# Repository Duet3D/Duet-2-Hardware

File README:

The Duet 3D Printer Controller design files repository.

The latest Duet hardware is the DuetWifi, see https://www.duet3d.com/ for more information

The recommended firmware is DC42's branch of the RepRapFirmware:
https://github.com/dc42/RepRapFirmware

Duet 2 Wifi and Duet 2 Ethernet
Design by Tony Lock and David Crocker
More info:
https://www.duet3d.com/
LICENSE: see the LICENSE file in the repository

Duet 0.8.5
Design by Tony Lock, based on the Duet 0.6
More info here:
http://blog.think3dprint3d.com/2015/08/new-duet-electronics-version-085.html
LICENSE: http://www.ohwr.org/attachments/2388/cern_ohl_v_1_2.txt

Duet 0.6:
Design by Andy Hingston, Tony Lock, Adrian Bowyer with much advice from Chris Palmer.
More info here:
http://blog.think3dprint3d.com/2013/12/Duet-Arduino-Due-compatible-3DPrinter-controller.html
LICENSE: http://www.ohwr.org/attachments/2388/cern_ohl_v_1_2.txt

Developed in KiCAD: http://www.kicad-pcb.org/display/KICAD/KiCad+EDA+Software+Suite

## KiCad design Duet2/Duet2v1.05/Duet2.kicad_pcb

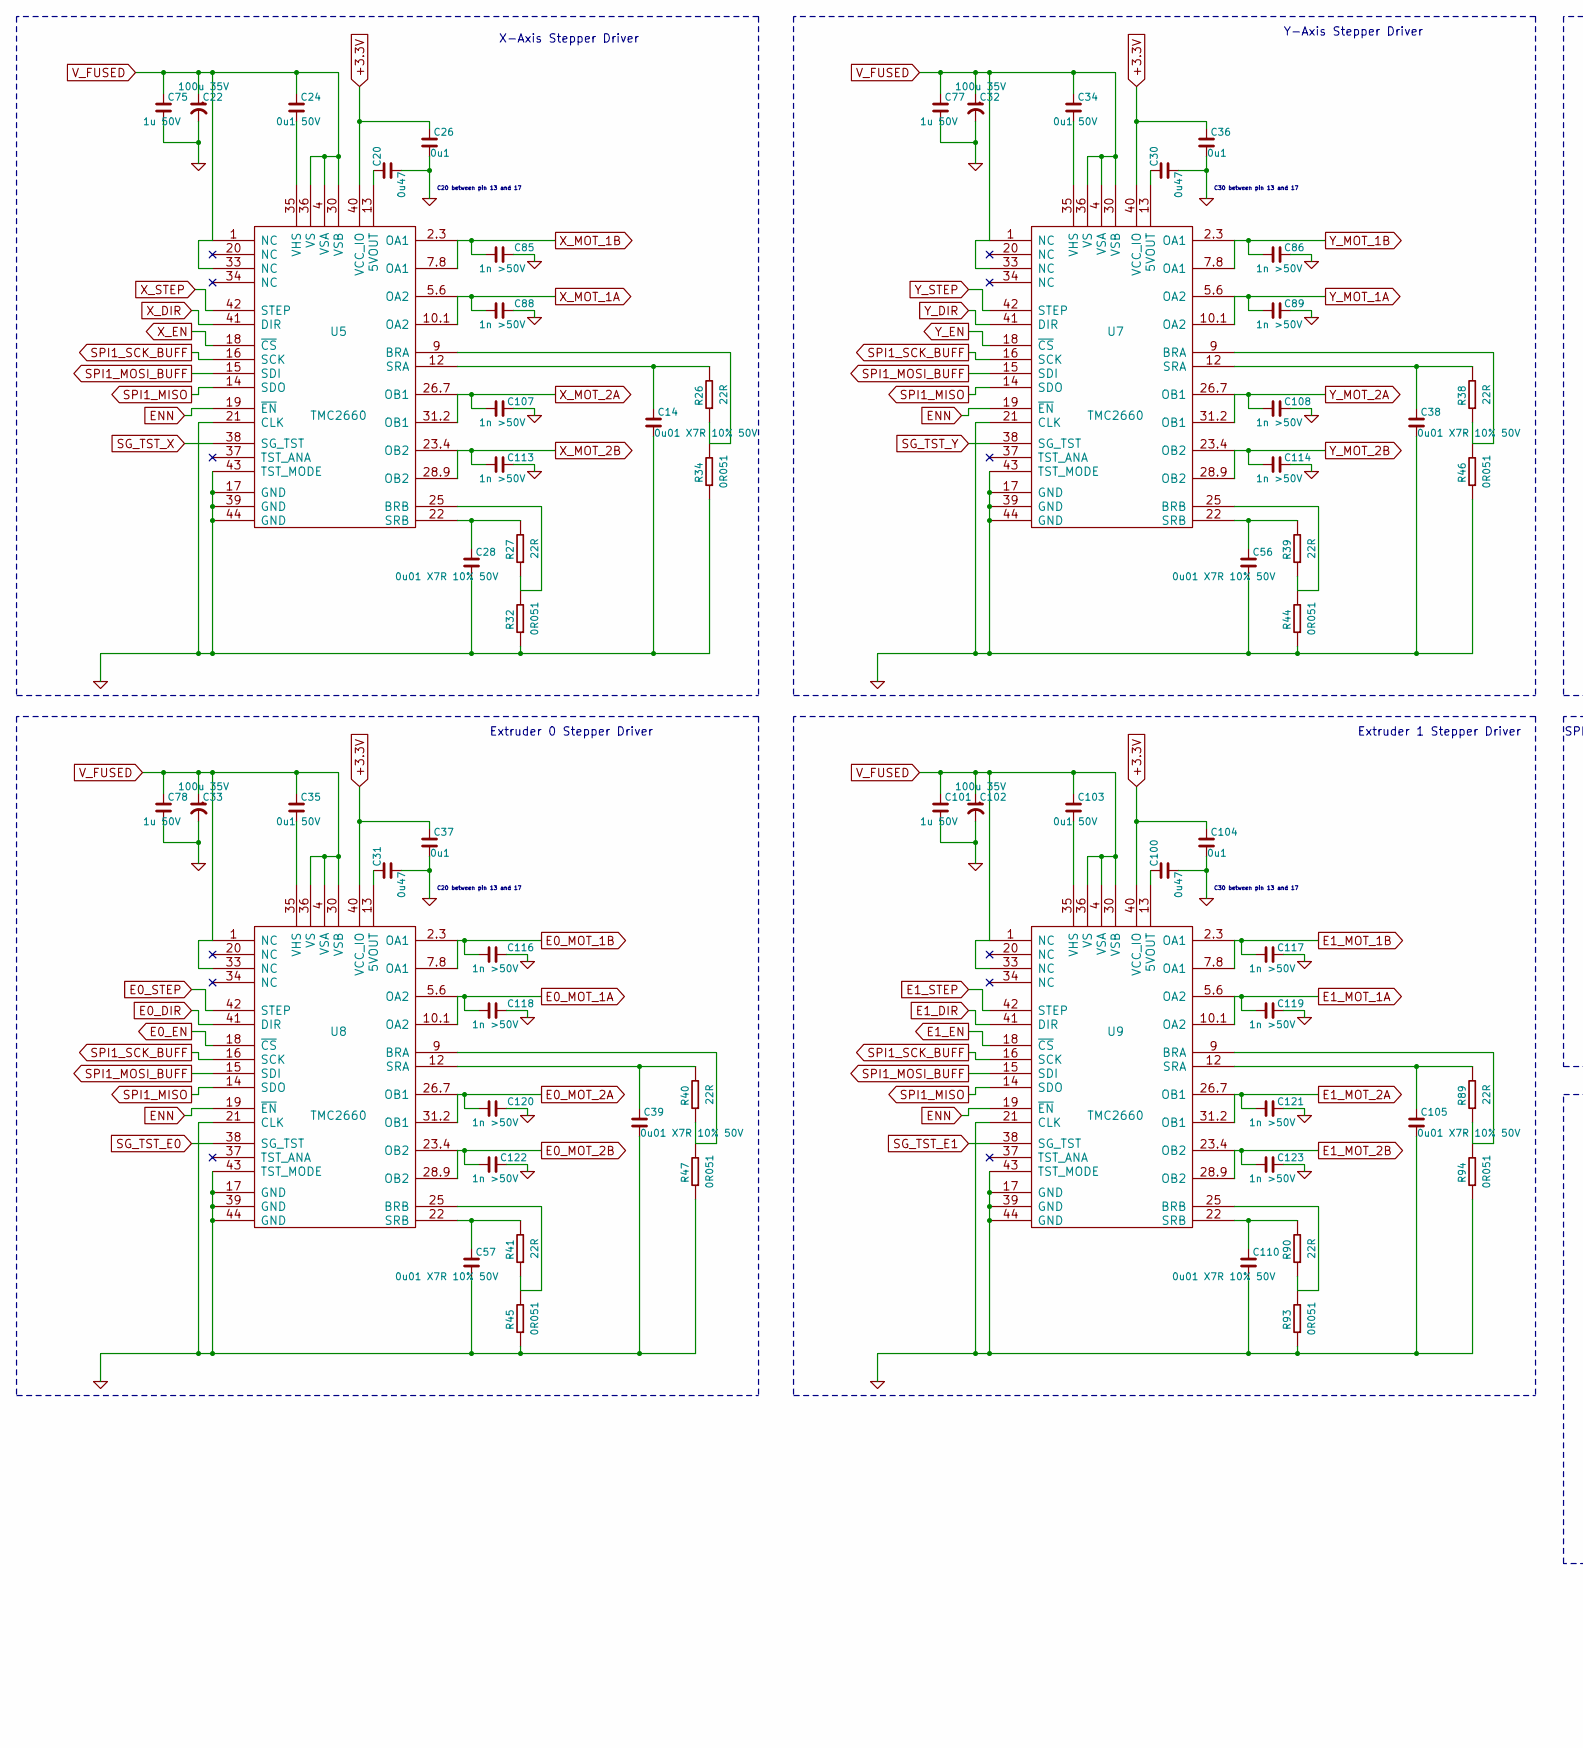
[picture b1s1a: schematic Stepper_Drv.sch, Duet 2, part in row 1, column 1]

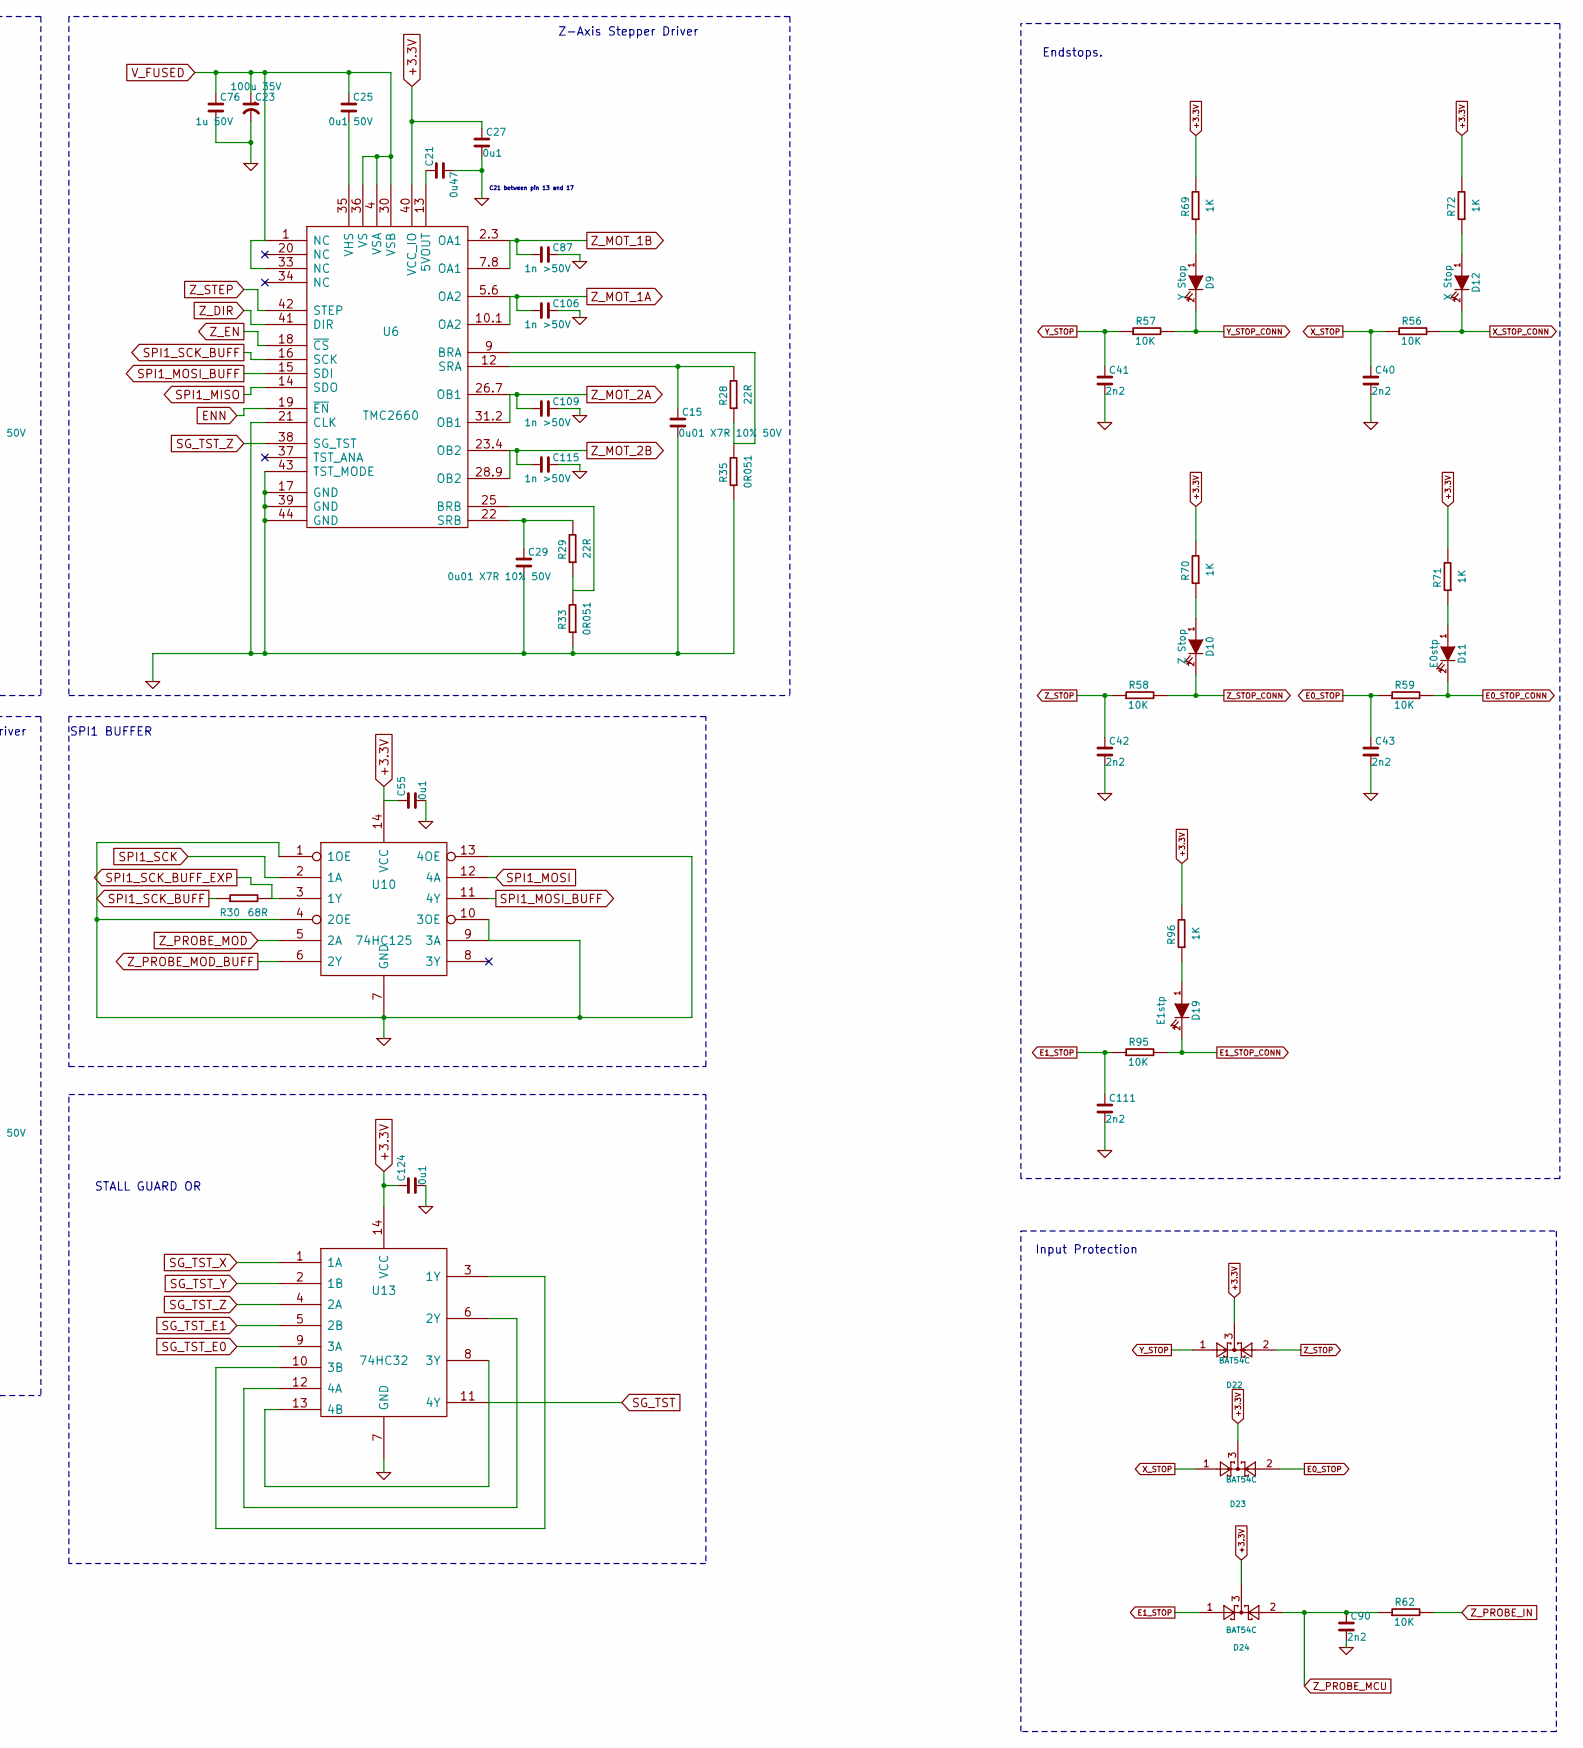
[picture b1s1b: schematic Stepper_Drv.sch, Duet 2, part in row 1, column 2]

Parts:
C14, C15, C28, C29, C38, C39, C56, C57, C105, C110: 0u01 X7R 10% 50V; C_0603
C20, C21, C30, C31, C100: 0u47; C_0603
C22, C23, C32, C33, C102: 100u 35V; C_ELEC_6.3x7.7
C24, C25, C34, C35, C103: 0u1 50V; C_0603
C26, C27, C36, C37, C55, C104, C124: 0u1; C_0603
C40, C41, C42, C43, C90, C111: 2n2; C_0603
C75, C76, C77, C78, C101: 1u 50V; C_0603
C85, C86, C87, C88, C89, C106, C107, C108, C109, C113, C114, C115, C116, C117, C118, C119, C120, C121, C122, C123: 1n >50V; C_0603
D9: Y Stop; D_0603
D10: Z Stop; D_0603
D11: E0stp; D_0603
D12: X Stop; D_0603
D19: E1stp; D_0603
D22, D23, D24: BAT54C; SOT-23-D
R26, R27, R28, R29, R38, R39, R40, R41, R89, R90: 22R; R_0603
R30: 68R; R_0603
R32, R33, R34, R35, R44, R45, R46, R47, R93, R94: 0R051; R_1206
R56, R57, R58, R59, R62, R95: 10K; R_0603
R69, R70, R71, R72, R96: 1K; R_0603
U5, U6, U7, U8, U9: TMC2660
U10: 74HC125; TSSOP-14
U13: 74HC32; TSSOP-14

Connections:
+3.3V: C26.1, C27.1, C36.1, C37.1, C55.1, C104.1, C124.1, D22.3, D23.3, D24.3, R69.2, R70.2, R71.2, R72.2, R96.2, U5.40 (VCC_IO), U6.40 (VCC_IO), U7.40 (VCC_IO), U8.40 (VCC_IO), U9.40 (VCC_IO), U10.14 (VCC), U13.14 (VCC); also elsewhere on the board
E0_DIR: U8.41 (DIR); also elsewhere on the board
E0_EN: U8.18 (~CS); also elsewhere on the board
E0_MOT_1A: C118.2, U8.5.6 (OA2), U8.10.1 (OA2); also elsewhere on the board
E0_MOT_1B: C116.2, U8.2.3 (OA1), U8.7.8 (OA1); also elsewhere on the board
E0_MOT_2A: C120.2, U8.26.7 (OB1), U8.31.2 (OB1); also elsewhere on the board
E0_MOT_2B: C122.2, U8.23.4 (OB2), U8.28.9 (OB2); also elsewhere on the board
E0_STEP: U8.42 (STEP); also elsewhere on the board
E0_STOP: C43.1, D23.2, R59.1; also elsewhere on the board
E0_STOP_CONN: D11.2 (K), R59.2; also elsewhere on the board
E1_DIR: U9.41 (DIR); also elsewhere on the board
E1_EN: U9.18 (~CS); also elsewhere on the board
E1_MOT_1A: C119.2, U9.5.6 (OA2), U9.10.1 (OA2); also elsewhere on the board
E1_MOT_1B: C117.2, U9.2.3 (OA1), U9.7.8 (OA1); also elsewhere on the board
E1_MOT_2A: C121.2, U9.26.7 (OB1), U9.31.2 (OB1); also elsewhere on the board
E1_MOT_2B: C123.2, U9.23.4 (OB2), U9.28.9 (OB2); also elsewhere on the board
E1_STEP: U9.42 (STEP); also elsewhere on the board
E1_STOP: C111.1, D24.1, R95.1; also elsewhere on the board
E1_STOP_CONN: D19.2 (K), R95.2; also elsewhere on the board
ENN: U5.19 (~EN), U6.19 (~EN), U7.19 (~EN), U8.19 (~EN), U9.19 (~EN); also elsewhere on the board
GND: C14.2, C15.2, C20.2, C21.2, C22.2, C23.2, C26.2, C27.2, C28.2, C29.2, C30.2, C31.2, C32.2, C33.2, C36.2, C37.2, C38.2, C39.2, C40.2, C41.2, C42.2, C43.2, C55.2, C56.2, C57.2, C75.2, C76.2, C77.2, C78.2, C85.1, C86.1, C87.1, C88.1, C89.1, C90.2, C100.2, C101.2, C102.2, C104.2, C105.2, C106.1, C107.1, C108.1, C109.1, C110.2, C111.2, C113.1, C114.1, C115.1, C116.1, C117.1, C118.1, C119.1, C120.1, C121.1, C122.1, C123.1, C124.2, R32.1, R33.1, R34.1, R35.1, R44.1, R45.1, R46.1, R47.1, R93.1, R94.1, U5.17 (GND), U5.21 (CLK), U5.39 (GND), U5.43 (TST_MODE), U5.44 (GND), U6.17 (GND), U6.21 (CLK), U6.39 (GND), U6.43 (TST_MODE), U6.44 (GND), U7.17 (GND), U7.21 (CLK), U7.39 (GND), U7.43 (TST_MODE), U7.44 (GND), U8.17 (GND), U8.21 (CLK), U8.39 (GND), U8.43 (TST_MODE), U8.44 (GND), U9.17 (GND), U9.21 (CLK), U9.39 (GND), U9.43 (TST_MODE), U9.44 (GND), U10.1 (1OE), U10.4 (2OE), U10.7 (GND), U10.9 (3A), U10.10 (3OE), U10.13 (4OE), U13.7 (GND); also elsewhere on the board
unnamed: C14.1, R26.2, U5.12 (SRA)
unnamed: C15.1, R28.2, U6.12 (SRA)
unnamed: C20.1, U5.13 (5VOUT)
unnamed: C21.1, U6.13 (5VOUT)
unnamed: C24.2, U5.35 (VHS)
unnamed: C25.2, U6.35 (VHS)
unnamed: C28.1, R27.2, U5.22 (SRB)
unnamed: C29.1, R29.2, U6.22 (SRB)
unnamed: C30.1, U7.13 (5VOUT)
unnamed: C31.1, U8.13 (5VOUT)
unnamed: C34.2, U7.35 (VHS)
unnamed: C35.2, U8.35 (VHS)
unnamed: C38.1, R38.2, U7.12 (SRA)
unnamed: C39.1, R40.2, U8.12 (SRA)
unnamed: C56.1, R39.2, U7.22 (SRB)
unnamed: C57.1, R41.2, U8.22 (SRB)
unnamed: C100.1, U9.13 (5VOUT)
unnamed: C103.2, U9.35 (VHS)
unnamed: C105.1, R89.2, U9.12 (SRA)
unnamed: C110.1, R90.2, U9.22 (SRB)
unnamed: D9.1 (A), R69.1
unnamed: D10.1 (A), R70.1
unnamed: D11.1 (A), R71.1
unnamed: D12.1 (A), R72.1
unnamed: D19.1 (A), R96.1
unnamed: R26.1, R34.2, U5.9 (BRA)
unnamed: R27.1, R32.2, U5.25 (BRB)
unnamed: R28.1, R35.2, U6.9 (BRA)
unnamed: R29.1, R33.2, U6.25 (BRB)
unnamed: R38.1, R46.2, U7.9 (BRA)
unnamed: R39.1, R44.2, U7.25 (BRB)
unnamed: R40.1, R47.2, U8.9 (BRA)
unnamed: R41.1, R45.2, U8.25 (BRB)
unnamed: R89.1, R94.2, U9.9 (BRA)
unnamed: R90.1, R93.2, U9.25 (BRB)
unnamed: U13.3 (1Y), U13.10 (3B)
unnamed: U13.6 (2Y), U13.12 (4A)
unnamed: U13.8 (3Y), U13.13 (4B)
PB5/TDO: U13.11 (4Y); also elsewhere on the board
SG_TST_E0: U8.38 (SG_TST), U13.9 (3A)
SG_TST_E1: U9.38 (SG_TST), U13.5 (2B)
SG_TST_X: U5.38 (SG_TST), U13.1 (1A)
SG_TST_Y: U7.38 (SG_TST), U13.2 (1B)
SG_TST_Z: U6.38 (SG_TST), U13.4 (2A)
SPI1_MISO: U5.14 (SDO), U6.14 (SDO), U7.14 (SDO), U8.14 (SDO), U9.14 (SDO); also elsewhere on the board
SPI1_MOSI: U10.12 (4A); also elsewhere on the board
SPI1_MOSI_BUFF: U5.15 (SDI), U6.15 (SDI), U7.15 (SDI), U8.15 (SDI), U9.15 (SDI), U10.11 (4Y); also elsewhere on the board
SPI1_SCK: U10.2 (1A); also elsewhere on the board
SPI1_SCK_BUFF: R30.1, U5.16 (SCK), U6.16 (SCK), U7.16 (SCK), U8.16 (SCK), U9.16 (SCK); also elsewhere on the board
SPI1_SCK_BUFF_EXP: R30.2, U10.3 (1Y); also elsewhere on the board
V_FUSED: C22.1, C23.1, C24.1, C25.1, C32.1, C33.1, C34.1, C35.1, C75.1, C76.1, C77.1, C78.1, C101.1, C102.1, C103.1, U5.1 (NC), U5.4 (VSA), U5.30 (VSB), U5.33 (NC), U5.36 (VS), U6.1 (NC), U6.4 (VSA), U6.30 (VSB), U6.33 (NC), U6.36 (VS), U7.1 (NC), U7.4 (VSA), U7.30 (VSB), U7.33 (NC), U7.36 (VS), U8.1 (NC), U8.4 (VSA), U8.30 (VSB), U8.33 (NC), U8.36 (VS), U9.1 (NC), U9.4 (VSA), U9.30 (VSB), U9.33 (NC), U9.36 (VS); also elsewhere on the board
X_DIR: U5.41 (DIR); also elsewhere on the board
X_EN: U5.18 (~CS); also elsewhere on the board
X_MOT_1A: C88.2, U5.5.6 (OA2), U5.10.1 (OA2); also elsewhere on the board
X_MOT_1B: C85.2, U5.2.3 (OA1), U5.7.8 (OA1); also elsewhere on the board
X_MOT_2A: C107.2, U5.26.7 (OB1), U5.31.2 (OB1); also elsewhere on the board
X_MOT_2B: C113.2, U5.23.4 (OB2), U5.28.9 (OB2); also elsewhere on the board
X_STEP: U5.42 (STEP); also elsewhere on the board
X_STOP: C40.1, D23.1, R56.1; also elsewhere on the board
X_STOP_CONN: D12.2 (K), R56.2; also elsewhere on the board
Y_DIR: U7.41 (DIR); also elsewhere on the board
Y_EN: U7.18 (~CS); also elsewhere on the board
Y_MOT_1A: C89.2, U7.5.6 (OA2), U7.10.1 (OA2); also elsewhere on the board
Y_MOT_1B: C86.2, U7.2.3 (OA1), U7.7.8 (OA1); also elsewhere on the board
Y_MOT_2A: C108.2, U7.26.7 (OB1), U7.31.2 (OB1); also elsewhere on the board
Y_MOT_2B: C114.2, U7.23.4 (OB2), U7.28.9 (OB2); also elsewhere on the board
Y_STEP: U7.42 (STEP); also elsewhere on the board
Y_STOP: C41.1, D22.1, R57.1; also elsewhere on the board
Y_STOP_CONN: D9.2 (K), R57.2; also elsewhere on the board
Z_DIR: U6.41 (DIR); also elsewhere on the board
Z_EN: U6.18 (~CS); also elsewhere on the board
Z_MOT_1A: C106.2, U6.5.6 (OA2), U6.10.1 (OA2); also elsewhere on the board
Z_MOT_1B: C87.2, U6.2.3 (OA1), U6.7.8 (OA1); also elsewhere on the board
Z_MOT_2A: C109.2, U6.26.7 (OB1), U6.31.2 (OB1); also elsewhere on the board
Z_MOT_2B: C115.2, U6.23.4 (OB2), U6.28.9 (OB2); also elsewhere on the board
Z_PROBE_IN: R62.2; also elsewhere on the board
Z_PROBE_MCU: C90.1, D24.2, R62.1; also elsewhere on the board
Z_PROBE_MOD: U10.5 (2A); also elsewhere on the board
Z_PROBE_MOD_BUFF: U10.6 (2Y); also elsewhere on the board
Z_STEP: U6.42 (STEP); also elsewhere on the board
Z_STOP: C42.1, D22.2, R58.1; also elsewhere on the board
Z_STOP_CONN: D10.2 (K), R58.2; also elsewhere on the board

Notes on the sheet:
Endstops.
Extruder 0 Stepper Driver
Y-Axis Stepper Driver
X-Axis Stepper Driver
Extruder 1 Stepper Driver
SPI1 BUFFER
C20 between pin 13 and 17
C30 between pin 13 and 17
Z-Axis Stepper Driver
C21 between pin 13 and 17
STALL GUARD OR
Input Protection

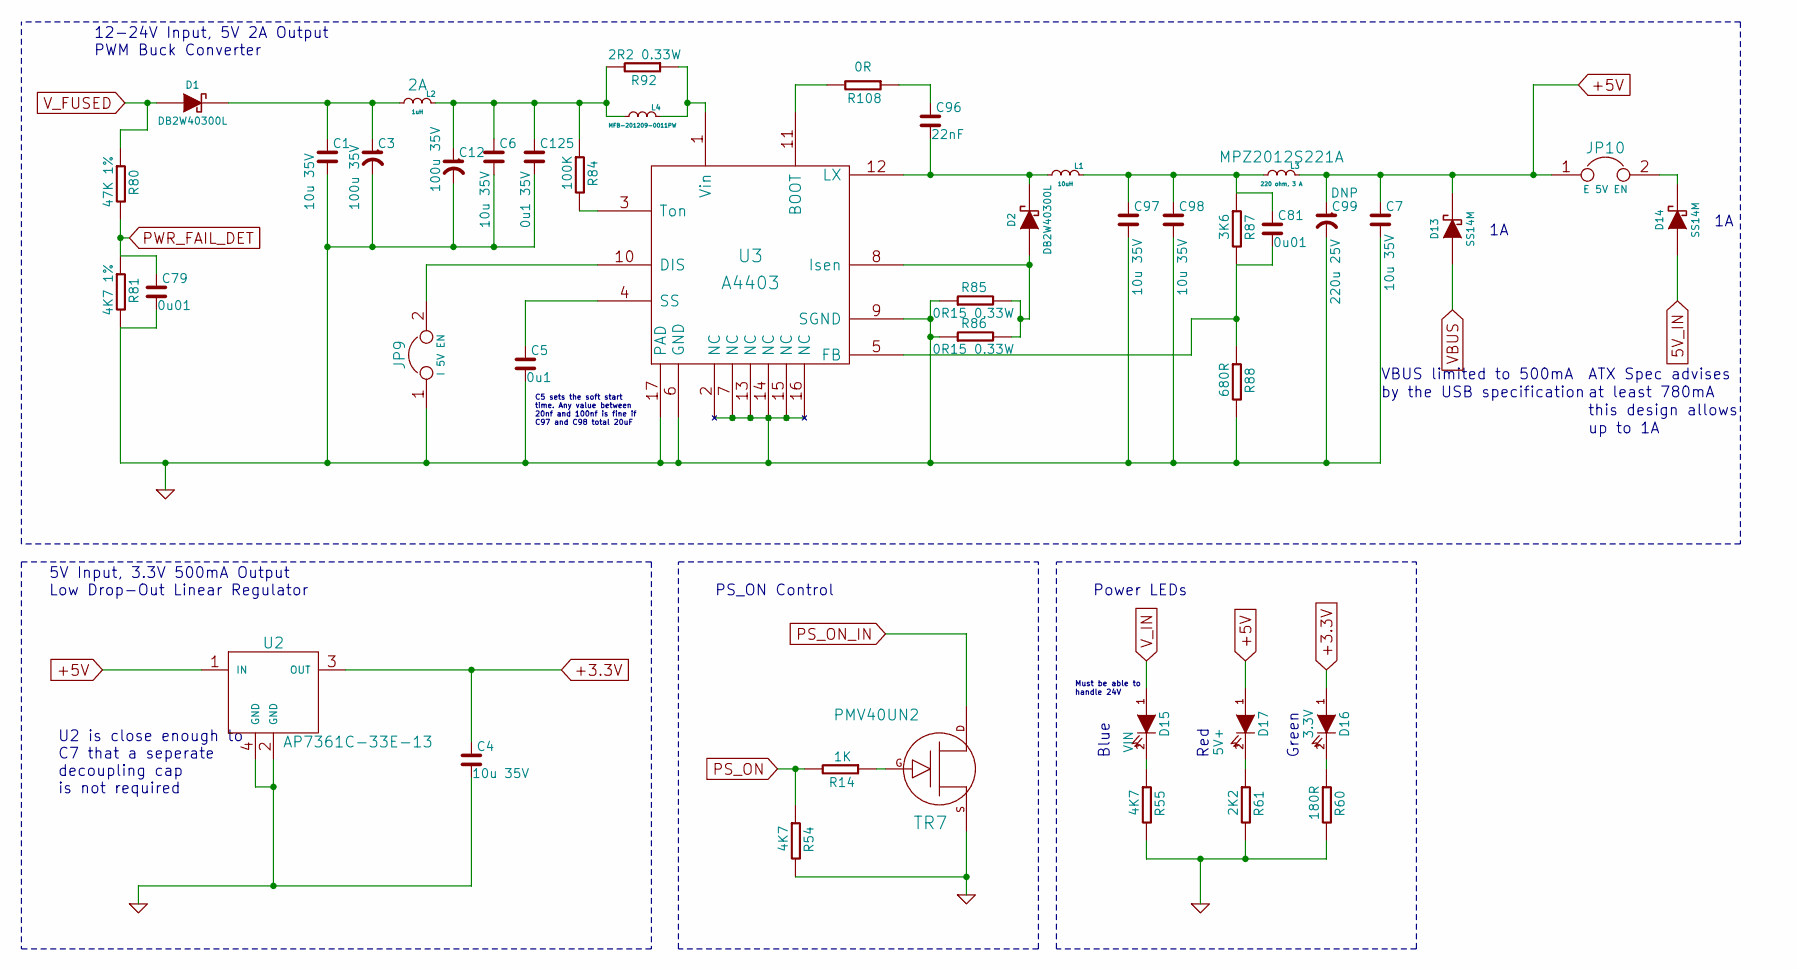
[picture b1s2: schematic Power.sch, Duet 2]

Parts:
C1, C4, C6, C7, C97, C98: 10u 35V; C_1206
C3, C12: 100u 35V; C_ELEC_6.3x7.7
C5: 0u1; C_0603
C79, C81: 0u01; C_0603
C96: 22nF; C_0603
C99: 220u 25V; C_ELEC_6.3x7.7; Rating DNP
C125: 0u1 35V; C_0603
D1, D2: DB2W40300L; D_SOD-123F
D13, D14: SS14M; uSMA
D15: VIN; D_0603
D16: 3.3V; D_0603
D17: 5V+; D_0603
JP9: I 5V EN; JUMPER
JP10: E 5V EN; JUMPER
L1: 10uH; L_6x6
L2: 1uH; C_1210; Rating 2A
L3: 220 ohm, 3 A; R_0805; Rating MPZ2012S221A
L4: MFB-201209-0011PW; R_0805
R14: 1K; R_0603
R54, R55: 4K7; R_0603
R60: 180R; R_0603
R61: 2K2; R_0603
R80: 47K 1%; R_0603
R81: 4K7 1%; R_0603
R84: 100K; R_0603
R85, R86: 0R15 0.33W; R_0805
R87: 3K6; R_0603
R88: 680R; R_0603
R92: 2R2 0.33W; R_0805
R108: 0R; R_0603
TR7: PMV40UN2; SOT-23
U2: AP7361C-33E-13; SOT-223
U3: A4403; QFN16-4x4

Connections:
5V_IN: D14.1 (A); also elsewhere on the board
+3.3V: C4.1, D16.1 (A), U2.3 (OUT); also elsewhere on the board
+5V: C7.1, C99.1, D13.2 (K), D17.1 (A), JP10.1, L3.1 (A), U2.1 (IN); also elsewhere on the board
GND: C1.2, C3.2, C4.2, C5.2, C6.2, C7.2, C12.2, C79.2, C97.2, C98.2, C99.2, C125.2, JP9.1, R54.2, R55.2, R60.2, R61.2, R81.2, R85.1, R86.1, R88.2, TR7.S, U2.2 (GND), U2.4 (GND), U3.2 (NC), U3.6 (GND), U3.7 (NC), U3.9 (SGND), U3.13 (NC), U3.14 (NC), U3.15 (NC), U3.16 (NC), U3.17 (PAD); also elsewhere on the board
unnamed: C1.1, C3.1, D1.1 (K), L2.2 (B)
unnamed: C5.1, U3.4 (SS)
unnamed: C6.1, C12.1, C125.1, L2.1 (A), L4.2 (B), R84.1, R92.2
unnamed: C81.1, C97.1, C98.1, L1.1 (A), L3.2 (B), R87.1
unnamed: C81.2, R87.2, R88.1, U3.5 (FB)
unnamed: C96.1, R108.1
unnamed: C96.2, D2.1 (K), L1.2 (B), U3.12 (LX)
unnamed: D2.2 (A), R85.2, R86.2, U3.8 (Isen)
unnamed: D14.2 (K), JP10.2
unnamed: D15.2 (K), R55.1
unnamed: D16.2 (K), R60.1
unnamed: D17.2 (K), R61.1
unnamed: JP9.2, U3.10 (DIS)
unnamed: L4.1 (A), R92.1, U3.1 (Vin)
unnamed: R14.1, TR7.G
unnamed: R84.2, U3.3 (Ton)
unnamed: R108.2, U3.11 (BOOT)
PS_ON: R14.2, R54.1; also elsewhere on the board
PS_ON_IN: TR7.D; also elsewhere on the board
PWR_FAIL_DET: C79.1, R80.2, R81.1; also elsewhere on the board
VBUS: D13.1 (A); also elsewhere on the board
V_FUSED: D1.2 (A), R80.1; also elsewhere on the board
V_IN: D15.1 (A); also elsewhere on the board

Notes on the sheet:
PS_ON Control
up to 1A
this design allows
at least 780mA
ATX Spec advises
by the USB specification
VBUS limited to 500mA
5V Input, 3.3V 500mA Output Low Drop-Out Linear Regulator
12-24V Input, 5V 2A Output PWM Buck Converter
C5 sets the soft start time. Any value between 20nf and 100nf is fine if C97 and C98 total 20uF
Power LEDs
Must be able to handle 24V
Blue
Red
Green
U2 is close enough to C7 that a seperate decoupling cap is not required

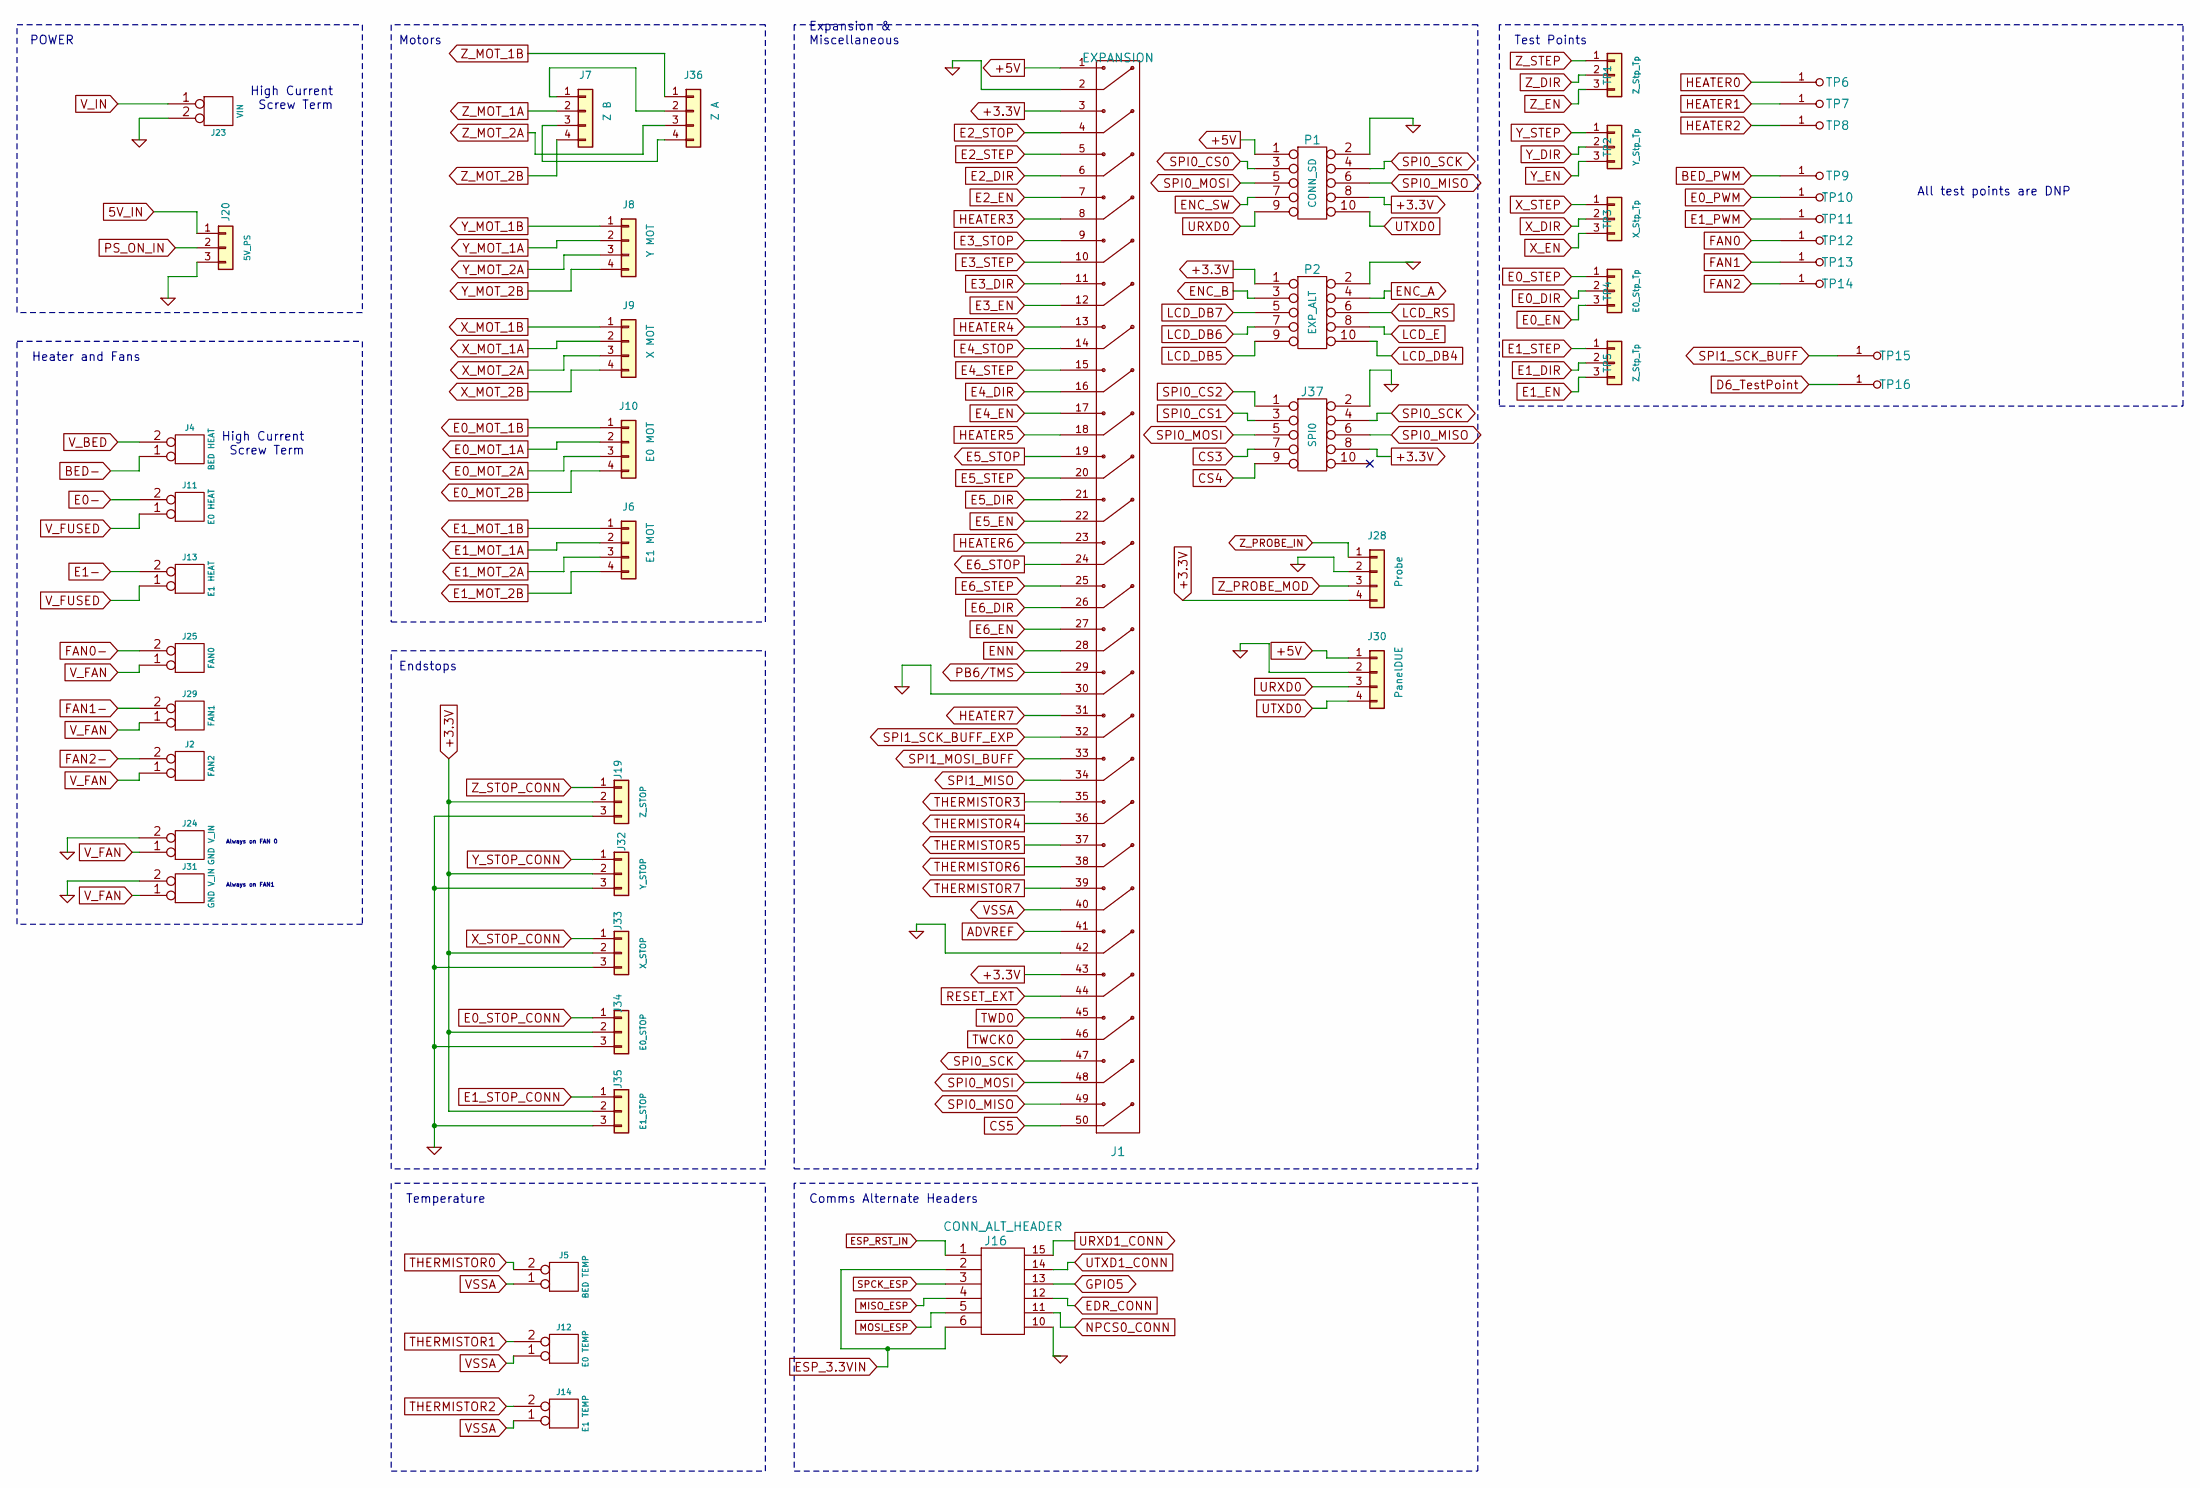
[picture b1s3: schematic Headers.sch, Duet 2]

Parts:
J1: EXPANSION; PIN_ARRAY_25X2
J2: FAN2; PIN_ARRAY_2X1
J4: BED HEAT; TERM_2-WAY_6.35mm
J5: BED TEMP; PIN_ARRAY_2X1
J6: E1 MOT; PIN_ARRAY_4x1
J7: Z B; PIN_ARRAY_4x1
J8: Y MOT; PIN_ARRAY_4x1
J9: X MOT; PIN_ARRAY_4x1
J10: E0 MOT; PIN_ARRAY_4x1
J11: E0 HEAT; 3.5MM_2X1
J12: E0 TEMP; PIN_ARRAY_2X1
J13: E1 HEAT; 3.5MM_2X1
J14: E1 TEMP; PIN_ARRAY_2X1
J16: CONN_ALT_HEADER; CONN_ALT_HEADER_v2
J19: Z_STOP; PIN_ARRAY_3X1
J20: 5V_PS; PIN_ARRAY_3X1
J23: VIN; TERM_2-WAY_6.35mm
J24, J31: GND V_IN; PIN_ARRAY_2X1
J25: FAN0; PIN_ARRAY_2X1
J28: Probe; PIN_ARRAY_4x1
J29: FAN1; PIN_ARRAY_2X1
J30: PanelDUE; PIN_ARRAY_4x1
J32: Y_STOP; PIN_ARRAY_3X1
J33: X_STOP; PIN_ARRAY_3X1
J34: E0_STOP; PIN_ARRAY_3X1
J35: E1_STOP; PIN_ARRAY_3X1
J36: Z A; PIN_ARRAY_4x1
J37: SPI0; MAX_TEMP_DB
P1: CONN_SD; IDC_PIN_ARRAY_5x2
P2: EXP_ALT; IDC_PIN_ARRAY_5x2
TP1, TP5: Z_Stp_Tp; CONN_3x1
TP2: Y_Stp_Tp; CONN_3x1
TP3: X_Stp_Tp; CONN_3x1
TP4: E0_Stp_Tp; CONN_3x1
TP6, TP7, TP8, TP9, TP10, TP11, TP12, TP13, TP14, TP15, TP16: TP; TP_via

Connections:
5V_IN: J20.1; also elsewhere on the board
+3.3V: J1.3, J1.43, J19.2, J28.4, J32.2, J33.2, J34.2, J35.2, J37.8, P1.8, P2.1; also elsewhere on the board
+5V: J1.1, J30.1, P1.1; also elsewhere on the board
ADVREF: J1.41; also elsewhere on the board
BED-: J4.1; also elsewhere on the board
BED_PWM: TP9.1; also elsewhere on the board
CS3: J37.7; also elsewhere on the board
CS4: J37.9; also elsewhere on the board
CS5: J1.50; also elsewhere on the board
D6_TestPoint: TP16.1; also elsewhere on the board
E0-: J11.2 (PM); also elsewhere on the board
E0_DIR: TP4.2; also elsewhere on the board
E0_EN: TP4.3; also elsewhere on the board
E0_MOT_1A: J10.2; also elsewhere on the board
E0_MOT_1B: J10.1; also elsewhere on the board
E0_MOT_2A: J10.3; also elsewhere on the board
E0_MOT_2B: J10.4; also elsewhere on the board
E0_PWM: TP10.1; also elsewhere on the board
E0_STEP: TP4.1; also elsewhere on the board
E0_STOP_CONN: J34.1; also elsewhere on the board
E1-: J13.2 (PM); also elsewhere on the board
E1_DIR: TP5.2; also elsewhere on the board
E1_EN: TP5.3; also elsewhere on the board
E1_MOT_1A: J6.2; also elsewhere on the board
E1_MOT_1B: J6.1; also elsewhere on the board
E1_MOT_2A: J6.3; also elsewhere on the board
E1_MOT_2B: J6.4; also elsewhere on the board
E1_PWM: TP11.1; also elsewhere on the board
E1_STEP: TP5.1; also elsewhere on the board
E1_STOP_CONN: J35.1; also elsewhere on the board
E2_DIR: J1.6; also elsewhere on the board
E2_EN: J1.7; also elsewhere on the board
E2_STEP: J1.5; also elsewhere on the board
E2_STOP: J1.4; also elsewhere on the board
E3_DIR: J1.11; also elsewhere on the board
E3_EN: J1.12; also elsewhere on the board
E3_STEP: J1.10; also elsewhere on the board
E3_STOP: J1.9; also elsewhere on the board
E4_DIR: J1.16; also elsewhere on the board
E4_EN: J1.17; also elsewhere on the board
E4_STEP: J1.15; also elsewhere on the board
E4_STOP: J1.14; also elsewhere on the board
E5_DIR: J1.21; also elsewhere on the board
E5_EN: J1.22; also elsewhere on the board
E5_STEP: J1.20; also elsewhere on the board
E5_STOP: J1.19; also elsewhere on the board
E6_DIR: J1.26; also elsewhere on the board
E6_EN: J1.27; also elsewhere on the board
E6_STEP: J1.25; also elsewhere on the board
E6_STOP: J1.24; also elsewhere on the board
EDR_CONN: J16.12; also elsewhere on the board
ENC_A: P2.4; also elsewhere on the board
ENC_B: P2.3; also elsewhere on the board
ENC_SW: P1.7; also elsewhere on the board
ENN: J1.28; also elsewhere on the board
ESP_3.3VIN: J16.2, J16.6; also elsewhere on the board
ESP_RST_IN: J16.1; also elsewhere on the board
FAN0: TP12.1; also elsewhere on the board
FAN0-: J25.2 (PM); also elsewhere on the board
FAN1: TP13.1; also elsewhere on the board
FAN1-: J29.2 (PM); also elsewhere on the board
FAN2: TP14.1; also elsewhere on the board
FAN2-: J2.2 (PM); also elsewhere on the board
GND: J1.2, J1.30, J1.42, J16.10, J19.3, J20.3, J23.2 (PM), J24.2 (PM), J28.2, J30.2, J31.2 (PM), J32.3, J33.3, J34.3, J35.3, J37.2, P1.2, P2.2; also elsewhere on the board
GPIO5: J16.13; also elsewhere on the board
HEATER0: TP6.1; also elsewhere on the board
HEATER1: TP7.1; also elsewhere on the board
HEATER2: TP8.1; also elsewhere on the board
HEATER3: J1.8; also elsewhere on the board
HEATER4: J1.13; also elsewhere on the board
HEATER5: J1.18; also elsewhere on the board
HEATER6: J1.23; also elsewhere on the board
HEATER7: J1.31; also elsewhere on the board
LCD_DB4: P2.10; also elsewhere on the board
LCD_DB5: P2.9; also elsewhere on the board
LCD_DB6: P2.7; also elsewhere on the board
LCD_DB7: P2.5; also elsewhere on the board
LCD_E: P2.8; also elsewhere on the board
LCD_RS: P2.6; also elsewhere on the board
MISO: J16.4; also elsewhere on the board
MOSI_ESP: J16.5; also elsewhere on the board
NPCS0_CONN: J16.11; also elsewhere on the board
unnamed: J7.1, J36.2
unnamed: J7.3, J36.4
PB6/TMS: J1.29; also elsewhere on the board
PS_ON_IN: J20.2; also elsewhere on the board
RESET_EXT: J1.44; also elsewhere on the board
SPCK_ESP: J16.3; also elsewhere on the board
SPI0_CS0: P1.3; also elsewhere on the board
SPI0_CS1: J37.3; also elsewhere on the board
SPI0_CS2: J37.1; also elsewhere on the board
SPI0_MISO: J1.49, J37.6, P1.6; also elsewhere on the board
SPI0_MOSI: J1.48, J37.5, P1.5; also elsewhere on the board
SPI0_SCK: J1.47, J37.4, P1.4; also elsewhere on the board
SPI1_MISO: J1.34; also elsewhere on the board
SPI1_MOSI_BUFF: J1.33; also elsewhere on the board
SPI1_SCK_BUFF: TP15.1; also elsewhere on the board
SPI1_SCK_BUFF_EXP: J1.32; also elsewhere on the board
THERMISTOR0: J5.2 (PM); also elsewhere on the board
THERMISTOR1: J12.2 (PM); also elsewhere on the board
THERMISTOR2: J14.2 (PM); also elsewhere on the board
THERMISTOR3: J1.35; also elsewhere on the board
THERMISTOR4: J1.36; also elsewhere on the board
THERMISTOR5: J1.37; also elsewhere on the board
THERMISTOR6: J1.38; also elsewhere on the board
THERMISTOR7: J1.39; also elsewhere on the board
TWCK0: J1.46; also elsewhere on the board
TWD0: J1.45; also elsewhere on the board
URXD0: J30.3, P1.9; also elsewhere on the board
URXD1_CONN: J16.15; also elsewhere on the board
UTXD0: J30.4, P1.10; also elsewhere on the board
UTXD1_CONN: J16.14; also elsewhere on the board
VSSA: J1.40, J5.1, J12.1, J14.1; also elsewhere on the board
V_BED: J4.2 (PM); also elsewhere on the board
V_FAN: J2.1, J24.1, J25.1, J29.1, J31.1; also elsewhere on the board
V_FUSED: J11.1, J13.1; also elsewhere on the board
V_IN: J23.1; also elsewhere on the board
X_DIR: TP3.2; also elsewhere on the board
X_EN: TP3.3; also elsewhere on the board
X_MOT_1A: J9.2; also elsewhere on the board
X_MOT_1B: J9.1; also elsewhere on the board
X_MOT_2A: J9.3; also elsewhere on the board
X_MOT_2B: J9.4; also elsewhere on the board
X_STEP: TP3.1; also elsewhere on the board
X_STOP_CONN: J33.1; also elsewhere on the board
Y_DIR: TP2.2; also elsewhere on the board
Y_EN: TP2.3; also elsewhere on the board
Y_MOT_1A: J8.2; also elsewhere on the board
Y_MOT_1B: J8.1; also elsewhere on the board
Y_MOT_2A: J8.3; also elsewhere on the board
Y_MOT_2B: J8.4; also elsewhere on the board
Y_STEP: TP2.1; also elsewhere on the board
Y_STOP_CONN: J32.1; also elsewhere on the board
Z_DIR: TP1.2; also elsewhere on the board
Z_EN: TP1.3; also elsewhere on the board
Z_MOT_1A: J7.2; also elsewhere on the board
Z_MOT_1B: J36.1; also elsewhere on the board
Z_MOT_2A: J36.3; also elsewhere on the board
Z_MOT_2B: J7.4; also elsewhere on the board
Z_PROBE_IN: J28.1; also elsewhere on the board
Z_PROBE_MOD: J28.3; also elsewhere on the board
Z_STEP: TP1.1; also elsewhere on the board
Z_STOP_CONN: J19.1; also elsewhere on the board

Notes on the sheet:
High Current Screw Term
Always on FAN 0
Always on FAN1
POWER
Heater and Fans
Temperature
Motors
Endstops
Expansion & Miscellaneous
Comms Alternate Headers
Test Points
All test points are DNP

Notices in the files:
Archive_Files/ASF_examples/LWIP_EXAMPLE1/LWIP_EXAMPLE1/src/ASF/sam/boards/sam3x_ek/sam3x_ek.h:
Copyright (c) 2011 - 2012 Atmel Corporation. All rights reserved.
Duet2/Duet2v1.05/Duet2.kicad_pcb:
CERN OHL 1.2
Ethernet_Module/EthernetModule.kicad_pcb:
Released under the terms of the Duet 3D license agreement:
